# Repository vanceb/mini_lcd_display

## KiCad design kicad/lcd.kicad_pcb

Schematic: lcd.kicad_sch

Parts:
C1, C2: 10u; C_0805_2012Metric_Pad1.18x1.45mm_HandSolder
D1, D2, D3, D4, D5, D6, D7, D8: WS2812B; LED_WS2812B_PLCC4_5.0x5.0mm_P3.2mm
J1: Power; PinHeader_1x02_P2.54mm_Horizontal
J2: Expansion; PinHeader_1x12_P2.54mm_Vertical
J3: I2C; PinHeader_1x04_P2.54mm_Horizontal
J4: Serial; PinHeader_1x04_P2.54mm_Horizontal
J5: Light; PinHeader_1x02_P2.54mm_Vertical
JP1: LED_Power; SolderJumper-3_P1.3mm_Bridged12_Pad1.0x1.5mm
JP2: Bypass; SolderJumper-2_P1.3mm_Open_Pad1.0x1.5mm
Q1: TSM2302CX; SOT-23_Handsoldering
R1: 10k; R_0603_1608Metric_Pad0.98x0.95mm_HandSolder
R2: LDR07; R_LDR_5.1x4.3mm_P3.4mm_Vertical
U1: DC->DC; Buck-Boost
U2: Geekcreit_ESP32_Devboard; geekcreit_dev_board
U3: D22-5003-03_LCD; D22-5003-03

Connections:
+5V: J1.1, J2.1, JP1.1 (A), U1.1, U2.50 (VIN)
+7.5V: C1.1, U1.2, U3.17 (LED+)
/LED_Power: C2.1, D1.1 (VDD), D2.1 (VDD), D3.1 (VDD), D4.1 (VDD), D5.1 (VDD), D6.1 (VDD), D7.1 (VDD), D8.1 (VDD), JP1.2 (C)
AMBIENT_LIGHT: J5.1, R1.2, R2.1, U2.10 (D34)
D13: J2.10, U2.20 (D13)
D14: J2.9, U2.17 (D14)
D19: J2.11, U2.38 (D19)
D25: J2.6, U2.14 (D25)
D26: J2.7, U2.15 (D26)
D27: J2.8, U2.16 (D27)
D32: J2.4, U2.12 (D32)
D33: J2.5, U2.13 (D33)
GND: C1.2, C2.2, D1.3 (VSS), D2.3 (VSS), D3.3 (VSS), D4.3 (VSS), D5.3 (VSS), D6.3 (VSS), D7.3 (VSS), D8.3 (VSS), J1.2, J2.12, J3.4, J4.4, J5.2, Q1.2 (S), R2.2, U1.3, U1.4, U2.49 (Gnd), U3.2 (VSS), U3.3 (PS)
I2C_CLK: J3.3, U2.39 (D22)
I2C_DATA: J3.2, U2.42 (D21)
LCD_BACKLIGHT_PWM: Q1.3 (D), U3.18 (LED-)
LCD_CLK: U2.35 (D18), U3.5 (DB6/SCLK)
LCD_DATA: U2.36 (D23), U3.4 (DB7/SID)
LCD_PWM: Q1.1 (G), U2.21 (D15)
LCD_RS: U2.24 (D4), U3.14 (RS)
LED_DATA: D1.4 (DIN), JP2.1 (A), U2.18 (D12)
LED_DATA_OUT: D8.2 (DOUT), J2.3, JP2.2 (B)
unnamed: D1.2 (DOUT), D2.4 (DIN)
unnamed: D2.2 (DOUT), D3.4 (DIN)
unnamed: D3.2 (DOUT), D4.4 (DIN)
unnamed: D4.2 (DOUT), D5.4 (DIN)
unnamed: D5.2 (DOUT), D6.4 (DIN)
unnamed: D6.2 (DOUT), D7.4 (DIN)
unnamed: D7.2 (DOUT), D8.4 (DIN)
RXDI: J4.3, U2.25 (RX2)
TXDO: J4.2, U2.27 (TX2)
~LCD_CS: U2.34 (D5), U3.16 (~CS)
~LCD_RESET: U2.22 (D2), U3.15 (~RESET)

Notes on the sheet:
128x32 Pixel LCD Display
ESP32 Dev Board
Ambient Light Measurement
Expansion Connectors
Power
RGB LEDs

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
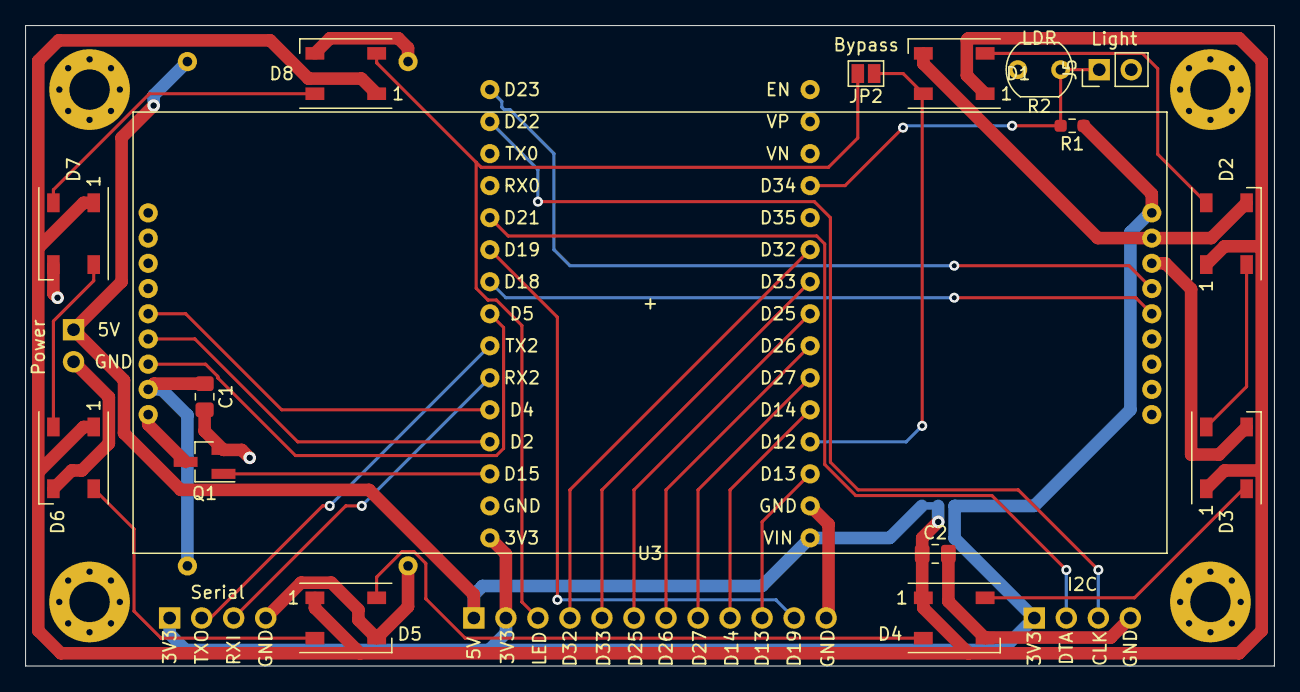
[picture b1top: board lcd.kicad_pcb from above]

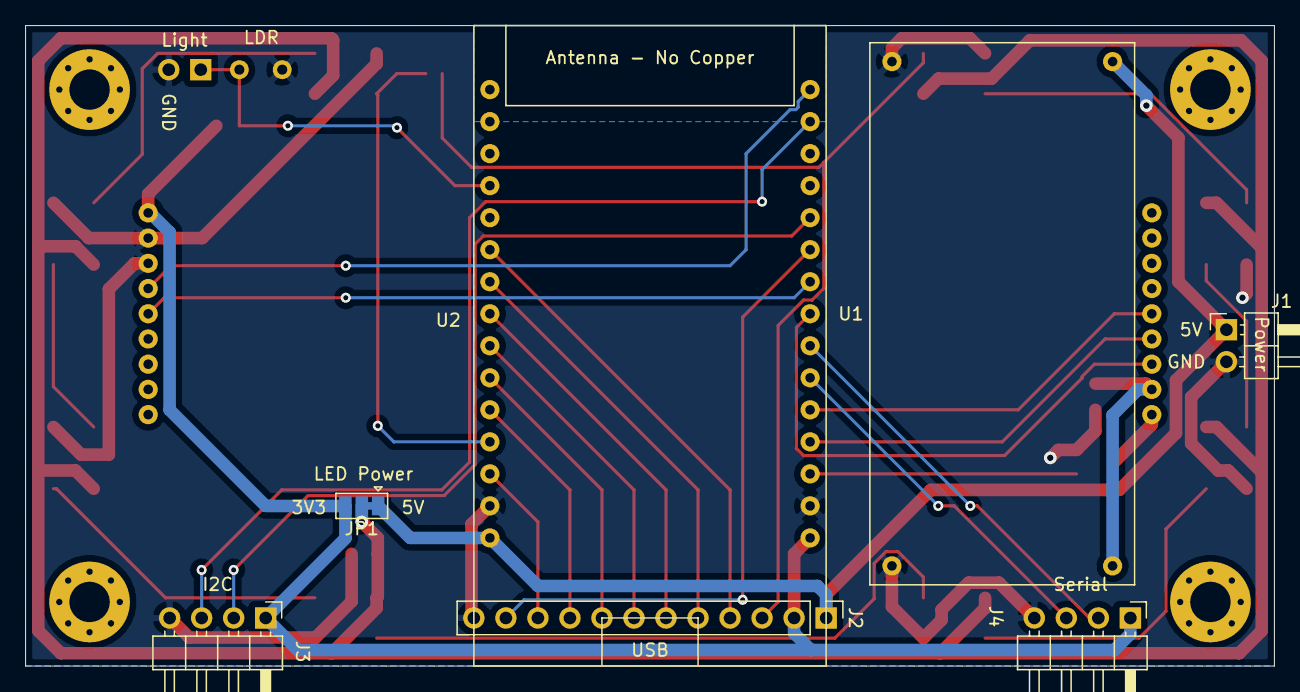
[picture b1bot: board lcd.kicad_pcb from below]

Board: 2 copper layers, 99.1 x 50.8 mm, 23 parts (7 on the bottom side), 34 nets.

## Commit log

2024-10-01 First commit after building prototype PCB
